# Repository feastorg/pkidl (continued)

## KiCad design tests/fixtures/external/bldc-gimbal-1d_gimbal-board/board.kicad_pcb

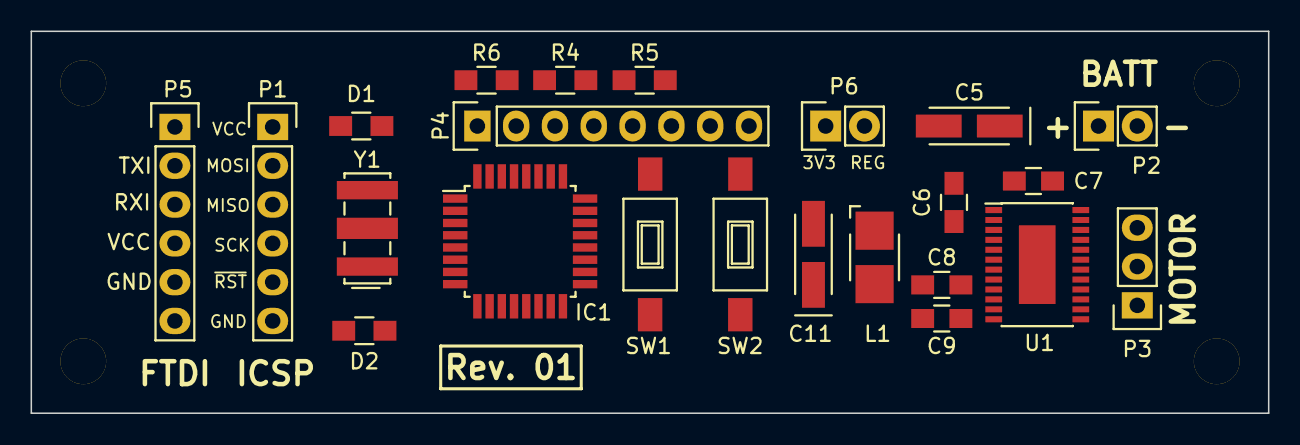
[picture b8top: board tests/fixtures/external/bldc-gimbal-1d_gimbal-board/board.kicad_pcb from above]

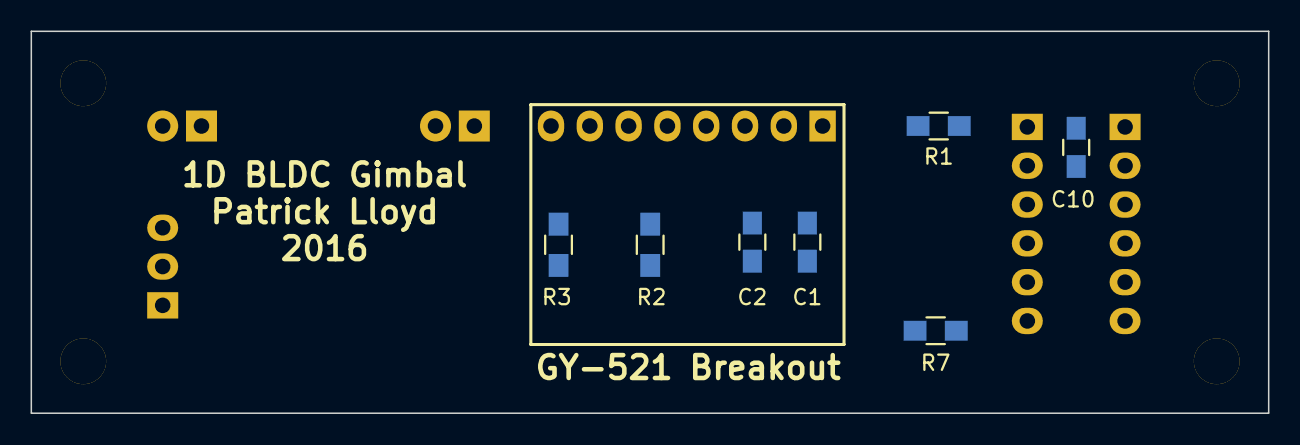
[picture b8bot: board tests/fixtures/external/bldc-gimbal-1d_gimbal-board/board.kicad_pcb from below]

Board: 2 copper layers, 81.0 x 25.0 mm, 34 parts (7 on the bottom side), 33 nets, no tracks yet.

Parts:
C1, C2, C6, C7, C10: 0.1uF; C_0805_HandSoldering
C5, C11: 10uF; TantalC_SizeA_EIA-3216_HandSoldering
C8, C9: 1uF; C_0805_HandSoldering
D1: RED; R_0805_HandSoldering
D2: GRN; R_0805_HandSoldering
H1, H2, H3, H4: CONN_01X01; MountingHole_3mm
IC1: ATMEGA328P-A; TQFP-32_7x7mm_Pitch0.8mm
L1: 47uH; Inductor_1212
P1: ICSP; Pin_Header_Straight_1x06
P2: BATT; Pin_Header_Straight_1x02
P3: MOTOR; Pin_Header_Straight_1x03
P4: IMU; Pin_Header_Straight_1x08
P5: FTDI; Pin_Header_Straight_1x06
P6: 3V3_CONN; Pin_Header_Straight_1x02
R1, R7: 330; R_0805_HandSoldering
R2, R3: 10K; R_0805_HandSoldering
R4, R5, R6: DNP; R_0805_HandSoldering
SW1, SW2: SW_PUSH; SW_SPST_FSMSM
U1: DRV10975; TSSOP-24_4.4x7.8mm_Pitch0.65mm_EP
Y1: Resonator; Resonator_7.2x3mm

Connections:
+3V3: C1.1, IC1.4, IC1.6, IC1.18, P1.1, P4.1, P5.4, P6.1, R1.1, R2.2, R3.2, R4.1, R5.1, R6.1
+BATT: C5.1, C7.2, P2.1, U1.23, U1.24
/ICSP_MISO: IC1.16, P1.3
/ICSP_MOSI: IC1.15, P1.2
/ICSP_SCK: IC1.17, P1.4
/IMU_INT: IC1.32, P4.8
/M_DIR: IC1.12, U1.14
/M_FG: IC1.1, R6.2, U1.12
/M_PHASE_U: P3.1, U1.17, U1.18
/M_PHASE_V: P3.2, U1.19, U1.20
/M_PHASE_W: P3.3, U1.21, U1.22
/M_SPEED: IC1.13, U1.13
/REG_OUT: C11.1, L1.2, P6.2, U1.6
/RESET: C10.1, IC1.29, P1.5, R2.1, SW1.1
/SCL: IC1.28, P4.3, R4.2, U1.10
/SDA: IC1.27, P4.4, R5.2, U1.11
/USART_DTR: C10.2, P5.1
/USART_RX: IC1.30, P5.3
/USART_TX: IC1.31, P5.2
/V3P3: C9.1, U1.9
GND: C1.2, C2.2, C5.2, C8.2, C9.2, C11.2, D1.1, D2.1, IC1.3, IC1.5, IC1.21, P1.6, P2.2, P4.2, P5.5, P5.6, SW1.2, SW2.2, U1.5, U1.8, U1.15, U1.16, U1.EP, Y1.2
unnamed: C2.1, IC1.20
unnamed: C6.1, U1.3
unnamed: C6.2, U1.2
unnamed: C7.1, U1.1
unnamed: C8.1, U1.7
unnamed: D1.2, R1.2
unnamed: D2.2, R7.2
unnamed: IC1.2, R3.1, SW2.1
unnamed: IC1.7, Y1.3
unnamed: IC1.8, Y1.1
unnamed: IC1.9, R7.1
unnamed: L1.1, U1.4
